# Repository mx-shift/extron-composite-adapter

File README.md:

# Extron Composite Adapter

A small, passive breakout board for connecting a composite video source and
stereo analog audio to an Extron IN1606 scaling presentation switcher.

The IN1606's two analog video inputs use 15-pin HD (VGA-style) connectors. They
accept composite video, but there's no RCA jack to plug a source into. This
board routes a standard yellow/white/red RCA jack block onto the HD-15 pins the
IN1606 expects for composite video, and breaks out the stereo audio to a
3.5 mm 5-position pluggable header.

It is a companion to the
[Extron S-Video Adapter](https://github.com/mx-shift/extron-svideo-adapter),
and shares its HD-15 and audio connections, board outline, and case design.

J1 is a female HD-15, like the IN1606's inputs, so connect the two with a
male-to-male HD-15 (VGA) cable. A cable with all 15 conductors isn't needed;
pins 2, 7 and 10 must be connected.

## Specifications

- 2-layer, 1.6 mm FR-4, 43.18 × 63.5 mm
- All through-hole parts; no active components
- Designed in KiCad 10

## Connectors

| Ref | Function             | Part |
|-----|----------------------|------|
| J1  | HD-15 to IN1606      | [Amphenol L77HDE15SD1CH4F](https://www.amphenol-cs.com/product/l77hde15sd1ch4f.html) |
| J2  | RCA video, L, R      | [Same Sky (formerly CUI Devices) RCJ-32234](https://www.sameskydevices.com/product/interconnect/audio-connectors/rca-jacks/rcj-32) (red, white, yellow) |
| J3  | Audio header         | [TE Connectivity 284512-5](https://www.te.com/en/product-284512-5.html) (3.5 mm, 5-pos) |

The HD-15 and audio wiring follow the "Analog Video Connection" pinout table
and "Analog Audio Connection" figure in the IN1606/IN1608 user guide (Extron
document 68-2290-01), available from the
[IN1606 product page](https://www.extron.com/product/in1606).

## Pinout

### Video

| Signal       | J2 (yellow RCA) | J1 (HD-15) |
|--------------|:---------------:|:----------:|
| Video        | 6 (centre)      | 2          |
| Video return | 5 (sleeve)      | 7          |
| Ground       | –               | 10, shell  |

All other HD-15 pins are unconnected. J2's two mounting posts sit in plated
holes with no connection.

### Audio

| Signal       | J2 (RCA)                    | J3 (header) |
|--------------|:---------------------------:|:-----------:|
| Left         | 4 (white centre)            | 1           |
| Right        | 2 (red centre)              | 4           |
| Audio ground | 1, 3 (red and white sleeve) | 2, 3, 5     |

Audio ground is kept separate from the video/chassis ground.

J3 is a pluggable header with the same 3.5 mm 5-position format as the
IN1606's audio inputs. Make the audio cable with a
[TE 284506-5](https://www.te.com/en/product-284506-5.html) screw-terminal plug
at each end, wired pin-for-pin (L+, L−, ⏚, R+, R−). This matches Extron's
unbalanced input wiring. The board already ties L− and R− to audio ground, so
don't add jumpers between − and ⏚ at the IN1606's plug.

## Revision history

- **Rev 1:** First design, derived from Rev 2 of the S-Video Adapter. Not yet
  fabricated or tested.

## Ordering boards

Download `extron-composite-adapter-<version>-oshpark.zip` from the
[latest release](https://github.com/mx-shift/extron-composite-adapter/releases/latest)
(or the `outputs` artifact of any Actions run). It contains the Gerbers and
the Excellon drill file. Upload the zip to [OSH Park](https://oshpark.com/).
The board is designed to OSH Park's 2-layer rules. Use the zip rather than the
`.kicad_pcb` file: the design is in KiCad 10 format, and OSH Park processes
uploaded board files with an older KiCad.

The release's `-bom.csv` lists the parts that solder to the board and imports
into DigiKey's BOM Manager. You'll also need:

- 2 × [TE Connectivity 284506-5](https://www.te.com/en/product-284506-5.html)
  3.5 mm 5-position screw-terminal plugs for the audio cable: one mates with
  J3 and the other with the IN1606's audio input. You can use the IN1606's own
  captive-screw plug for its end instead.
- 1 × male-to-male HD-15 (VGA) cable to connect J1 to the IN1606

## Case

`case/case.scad` is a two-part, 3D-printable case. The bottom shell holds the
board on ledges along its two connector-free edges, and walls inside the top
shell clamp the same strips from above. The top shell's side walls have
openings for the connectors. Ears on the bottom shell let you screw the case
to a surface. Assembled, it measures 47.8 × 84.1 × 30.6 mm (104 mm long
including the ears).

STLs for both shells are attached to each
[release](https://github.com/mx-shift/extron-composite-adapter/releases/latest)
and to every Actions run (the `case` artifact), already oriented for printing.

Hardware:

- 4 × M3 × 25 socket head cap screws
- 4 × M3 heat-set inserts for 4.0 mm holes, at least 5 mm long (set
  `insert_d` to about 2.6 to self-tap the screws instead)
- 4 × #8 or M4 screws to mount the case (4.5 mm holes)

Printing: PLA or PETG, 0.2 mm layers, no supports. Print the bottom shell
floor-down and the top shell roof-down, as exported.

Assembly: install the inserts in the bottom shell, drop the board in, lower
the top shell over the connectors, and fit the screws.

The connector openings are sized from the manufacturers' drawings. The
`check` part in `case.scad` verifies that the case doesn't intersect the board
or the connector bodies. Mating plugs with oversized bodies or overmolds may
stop against the walls before fully seating: the RCA slots are 13.5 mm wide,
leaving about 6 mm of each barrel outside the wall, and the audio plug opening
is 21.7 × 14 mm. The audio plug opening was not checked against the mating
plug's drawing. Adjust the parameters at the top of `case.scad` if needed.

## Building

`scripts/build.sh` runs ERC and DRC, then writes the schematic PDF, a BOM CSV
that imports into DigiKey's BOM Manager, and the OSH Park package to
`output/`. GitHub Actions runs it in the `kicad/kicad`
container on every push and pull request; pushing a `v*` tag also publishes a
release with the zip, schematic PDF, BOM, and case STLs. To run it locally:

```sh
scripts/build.sh
# or, with the KiCad Flatpak:
KICAD_CLI="flatpak run --command=kicad-cli org.kicad.KiCad" scripts/build.sh
```

`scripts/build-case.sh` runs the case collision check and exports the STLs to
`output-case/`. It needs OpenSCAD.

The source location printed on the board and in the title blocks is the
`SOURCE_URL` project text variable (Schematic/Board Setup → Text Variables).

## Repository layout

- `extron-composite-adapter.kicad_pro`, `.kicad_sch`, `.kicad_pcb`: KiCad
  project
- `extron-composite-adapter.pretty/`: custom footprints for the connectors
  above. The project library table (`fp-lib-table`) loads them automatically.
- `case/case.scad`: 3D-printable case (OpenSCAD)
- `scripts/build.sh`, `scripts/build-case.sh`, `.github/workflows/build.yml`:
  design checks, fabrication outputs, and case STLs

## License

Copyright Rick Altherr 2026.

This hardware design is licensed under the CERN Open Hardware Licence
Version 2 - Strongly Reciprocal (SPDX: `CERN-OHL-S-2.0`). See
[LICENSE](LICENSE) for the full text.

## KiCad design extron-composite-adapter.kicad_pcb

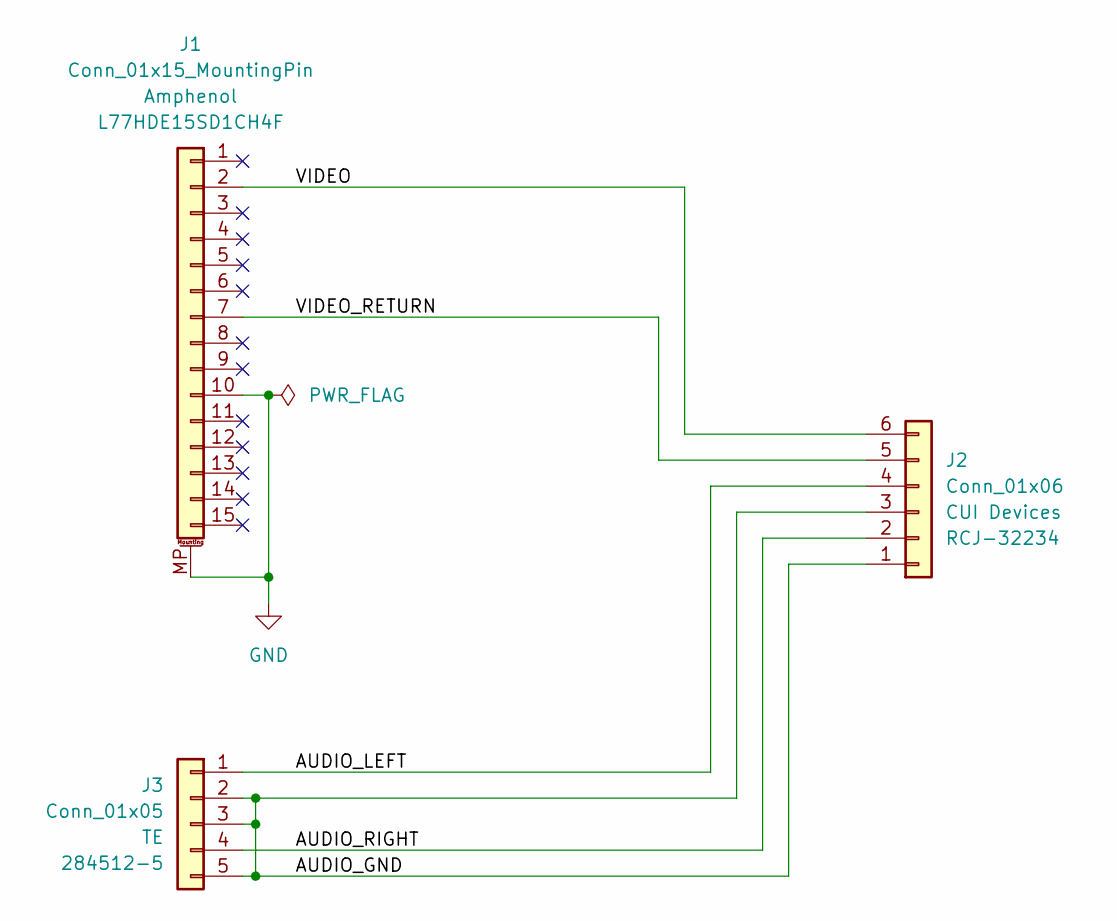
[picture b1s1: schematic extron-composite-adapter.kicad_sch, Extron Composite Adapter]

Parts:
J1: Conn_01x15_MountingPin; DSUB-15-HD_Female_Horizontal_P2.29x2.54mm_EdgePinOffset8.89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; Manufacturer Part Number L77HDE15SD1CH4F
J2: Conn_01x06; Jack_RCA_1x3_CUI_RCJ-32XXX_Horizontal_THT; Manufacturer Part Number RCJ-32234
J3: Conn_01x05; TerminalBlock_TE_284512-5_1x05_P3.5mm_Horizontal; Manufacturer Part Number 284512-5

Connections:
/AUDIO_GND: J2.1, J2.3, J3.2, J3.3, J3.5
/AUDIO_LEFT: J2.4, J3.1
/AUDIO_RIGHT: J2.2, J3.4
/VIDEO: J1.2, J2.6
/VIDEO_RETURN: J1.7, J2.5
GND: J1.10, J1.MP (MountPin)

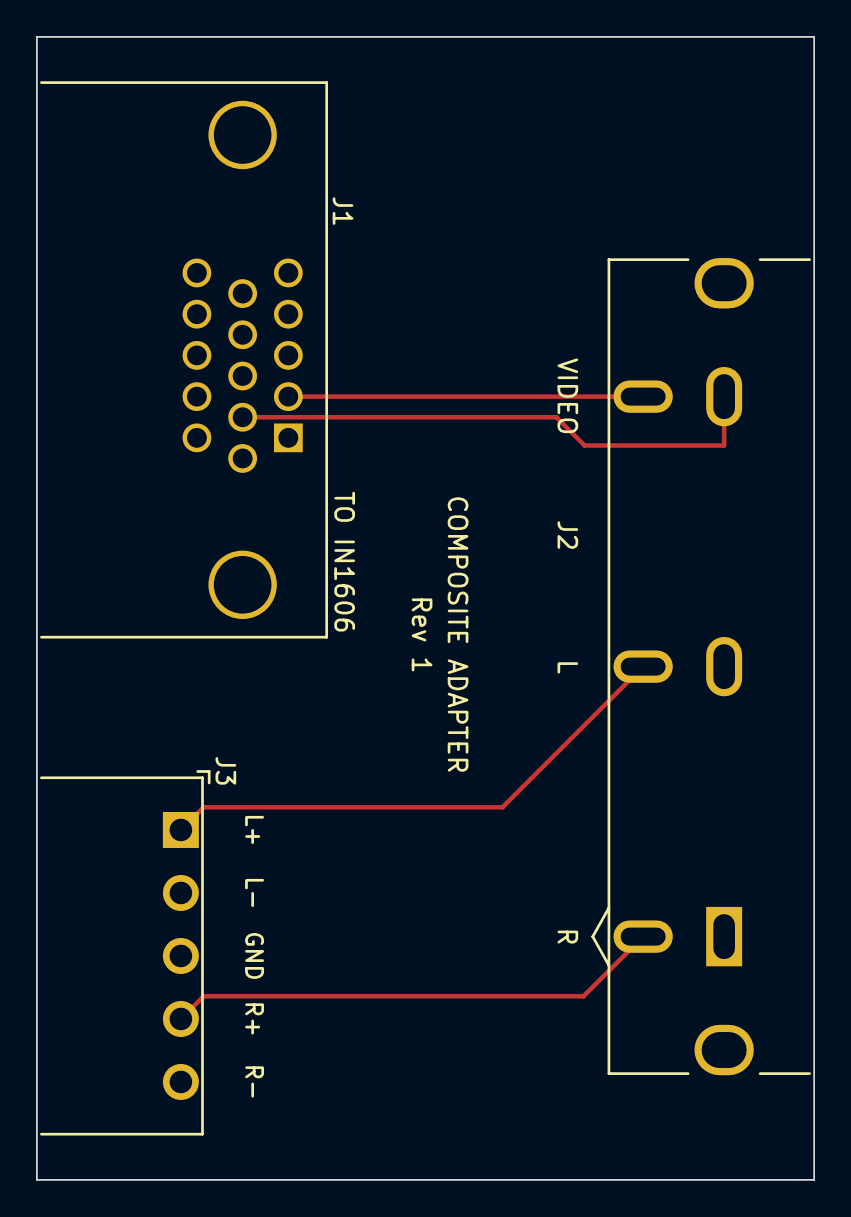
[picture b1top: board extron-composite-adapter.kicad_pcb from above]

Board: 2 copper layers, 43.2 x 63.5 mm, 3 parts (0 on the bottom side), 6 nets.

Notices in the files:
extron-composite-adapter.kicad_pcb:
Licensed under CERN-OHL-S-2.0
